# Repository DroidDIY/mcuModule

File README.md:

mcuModule
=========

Generic MCU module that can be used in any project that requires a microcontroller. Based around the ATmega328
microcontroller and is based on the Arduino Uno design.

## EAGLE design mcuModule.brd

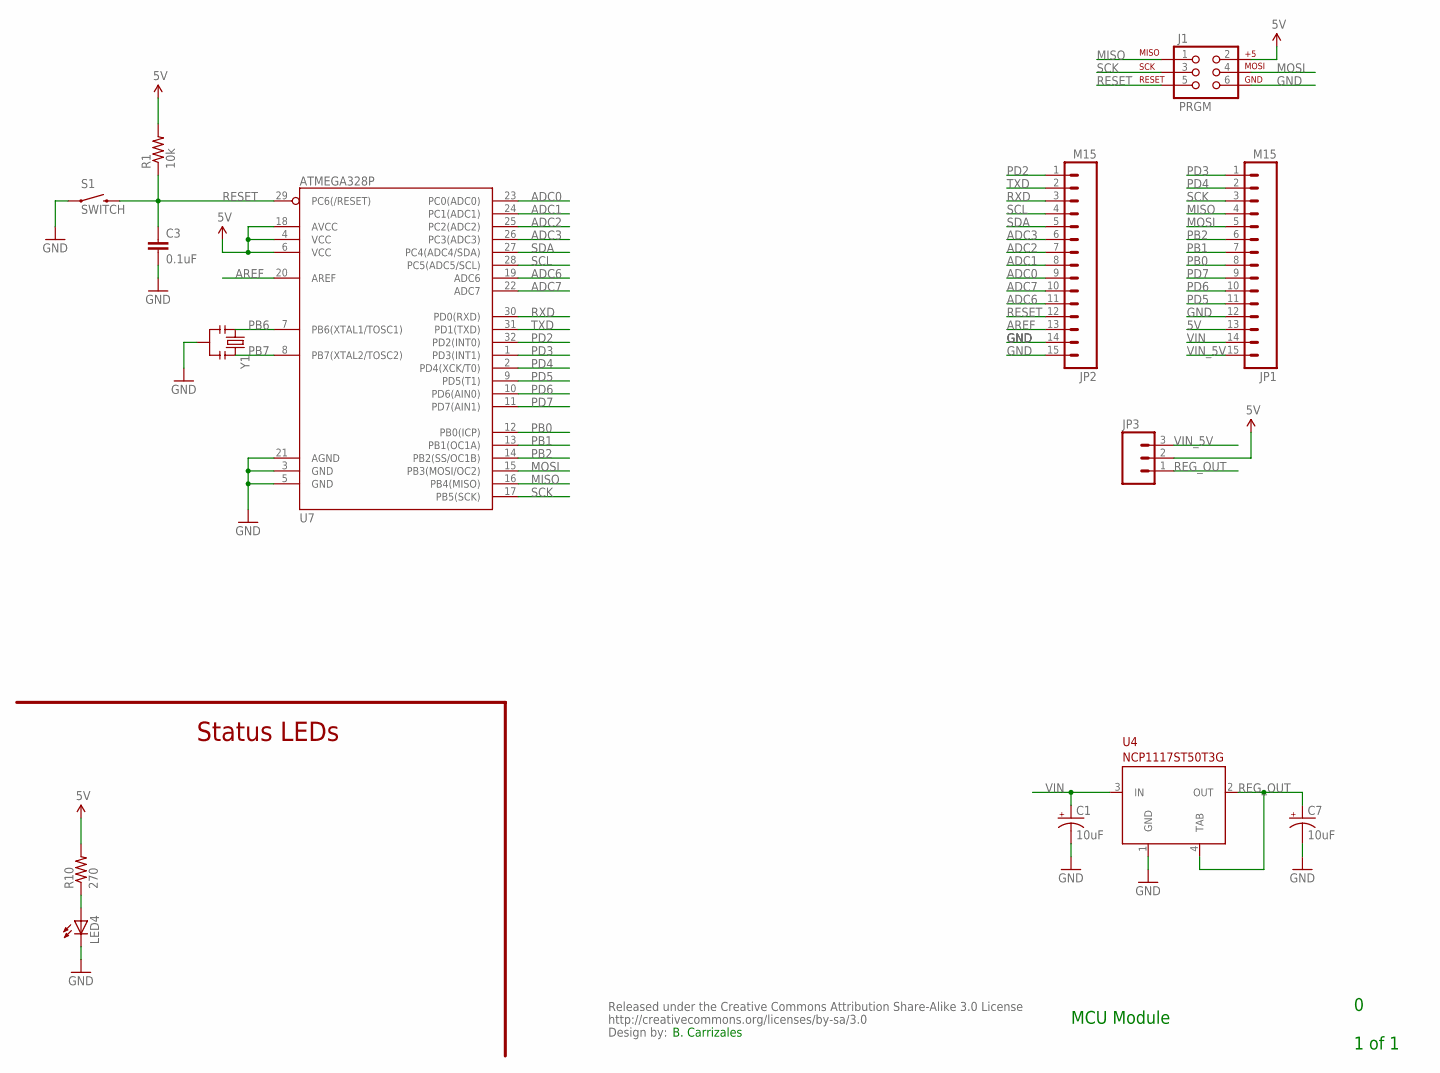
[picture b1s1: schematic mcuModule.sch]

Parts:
C1, C7: 10uF; PANASONIC_BMIN
C3: 0.1uF; 0603-CAP
CC_TEXT1: CREATIVE_COMMONS
J1: PRGM; 2X3
JP1, JP2: M15; 1X15
JP3: M03PTH; 1X03
LED4: LED0603; LED-0603
R1: 10k; 0603-RES
R10: 270; 0603-RES
S1: SWITCH; TACTILE_SWITCH_SMD
U4: NCP1117ST50T3G; SOT223
U7: ATMEGA328P; TQFP32-08
Y1: RESONATORPTH; RESONATOR-PTH

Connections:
5V: J1.2, JP1.13, JP3.2, R1.2, R10.2, U7.4 (VCC), U7.6 (VCC), U7.18 (AVCC)
ADC0: JP2.9, U7.23 (PC0(ADC0))
ADC1: JP2.8, U7.24 (PC1(ADC1))
ADC2: JP2.7, U7.25 (PC2(ADC2))
ADC3: JP2.6, U7.26 (PC3(ADC3))
ADC6: JP2.11, U7.19 (ADC6)
ADC7: JP2.10, U7.22 (ADC7)
AREF: JP2.13, U7.20 (AREF)
GND: C1.-, C3.2, C7.-, J1.6, JP1.12, JP2.14, JP2.15, LED4.C, S1.1, U4.1 (GND), U7.3 (GND), U7.5 (GND), U7.21 (AGND), Y1.2
MISO: J1.1, JP1.4, U7.16 (PB4(MISO))
MOSI: J1.4, JP1.5, U7.15 (PB3(MOSI/OC2))
unnamed: LED4.A, R10.1
PB0: JP1.8, U7.12 (PB0(ICP))
PB1: JP1.7, U7.13 (PB1(OC1A))
PB2: JP1.6, U7.14 (PB2(SS/OC1B))
PB6: U7.7 (PB6(XTAL1/TOSC1)), Y1.1
PB7: U7.8 (PB7(XTAL2/TOSC2)), Y1.3
PD2: JP2.1, U7.32 (PD2(INT0))
PD3: JP1.1, U7.1 (PD3(INT1))
PD4: JP1.2, U7.2 (PD4(XCK/T0))
PD5: JP1.11, U7.9 (PD5(T1))
PD6: JP1.10, U7.10 (PD6(AIN0))
PD7: JP1.9, U7.11 (PD7(AIN1))
REG_OUT: C7.+, JP3.1, U4.2 (OUT), U4.4 (TAB)
RESET: C3.1, J1.5, JP2.12, R1.1, S1.3 (2), U7.29 (PC6(/RESET))
RXD: JP2.3, U7.30 (PD0(RXD))
SCK: J1.3, JP1.3, U7.17 (PB5(SCK))
SCL: JP2.4, U7.28 (PC5(ADC5/SCL))
SDA: JP2.5, U7.27 (PC4(ADC4/SDA))
TXD: JP2.2, U7.31 (PD1(TXD))
VIN: C1.+, JP1.14, U4.3 (IN)
VIN_5V: JP1.15, JP3.3

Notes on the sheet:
MCU Module
1 of 1
B. Carrizales
Status LEDs

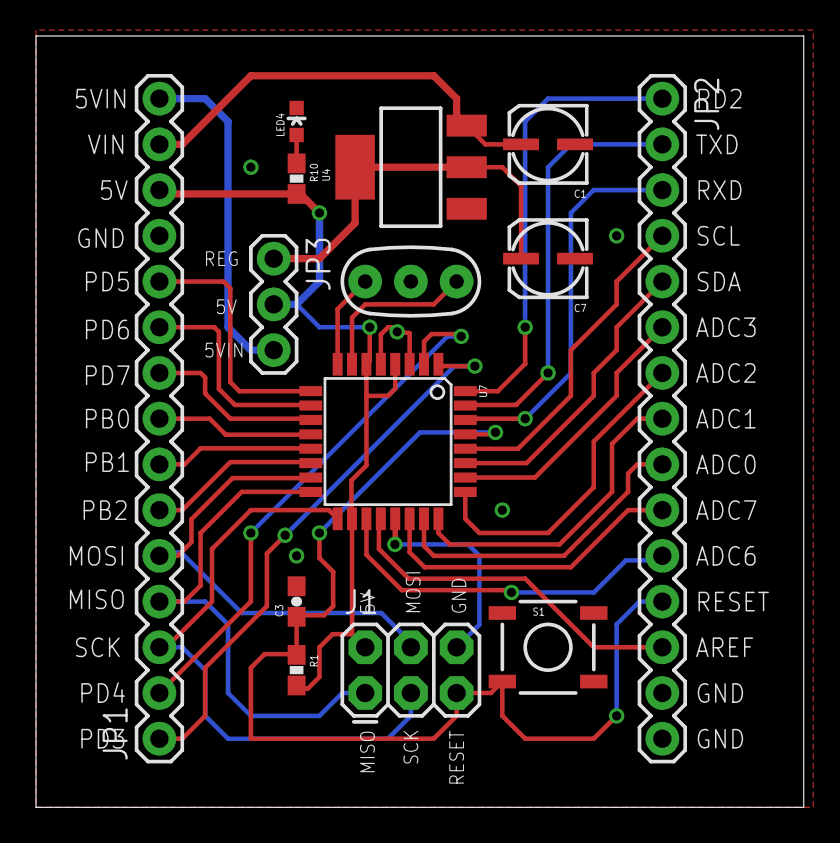
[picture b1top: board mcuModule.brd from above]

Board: 2 copper layers, 42.7 x 42.9 mm, 15 parts (0 on the bottom side), 32 nets.

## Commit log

2014-12-27 added schematic
2014-12-27 added board layout and gerber files

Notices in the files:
parts and their libraries:
SparkFun-Capacitors: Licensing: CC v3.0 Share-Alike You are welcome to use this library for commercial purposes.
SparkFun-Aesthetics: Released under the Creative Commons Attribution Share-Alike 3.0 License
SparkFun-Aesthetics: http://creativecommons.org/licenses/by-sa/3.0
